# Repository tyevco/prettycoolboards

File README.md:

# prettycoolboards

**Docs site:** <https://tyevco.github.io/prettycoolboards/>

Open hardware boards designed as code. The schematics and PCBs are generated
from Python into KiCad 10, routed with Freerouting plus a grid router, and
gated by ERC, DRC and schematic parity before any fab output is written.
Enclosures and mechanics are in build123d.

## Boards

| Board | Status | |
|---|---|---|
| [PrettyCool Caliper](caliper/README.md) | rev A in design | 150 mm digital caliper: magnetic and capacitive sensing, ESP32-S3 with BLE + Wi-Fi, colour IPS, reading memory, go/no-go, USB-C |
| [PrettyCool Keyboard](keyboard/README.md) | concept: researched, nothing designed | Analog keyboard designed as code: shear keys that point, a haptic thumb wheel, two-host KVM, a generated keywell, and a layout compiler with latency and battery gates. Rev A is a sensing testbed |

## Repository layout

```
tools/        shared Python → KiCad generator toolchain (see tools/README.md)
caliper/      one folder per board: hardware/, firmware/, app/, docs/
keyboard/     concept and research only (docs/), no hardware yet
.vitepress/   docs site (VitePress), published to GitHub Pages by .github/workflows/docs.yml
```

The hardware toolchain runs on Linux: KiCad 10 (`kicad-cli` + `pcbnew`), Java 21 +
Freerouting 2.1, ngspice and build123d. On Windows, run it in WSL.

```sh
npm ci && npm run docs:dev   # preview the docs site locally
```

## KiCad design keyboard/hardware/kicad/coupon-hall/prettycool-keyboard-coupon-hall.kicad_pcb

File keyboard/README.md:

# PrettyCool Keyboard (working name)

A planned analog keyboard designed as code: one layout file in, a gated, JLC-assembled board, case and firmware out.
The plan: keys that also point, and controls that change how they feel to suit what you are doing.

> **Status (2026-11-27): concept and rev A testbed design.** Nothing is built, ordered or measured. This folder holds
> the research, the feature roadmap the owner chose on 2026-11-25, the rev A MCU the owner chose on 2026-11-26
> ([decision record](docs/mcu.md)), three testbed decisions of the same day (no charger on rev A, the slot connector, a
> USB Type-C detect chip), and the owner's seven answers of 2026-11-27 to the [rev A risk register](docs/risks.md)
> (below). The testbed's [SPEC](hardware/design/SPEC.md) is its draft architecture of record. The test coupon and the
> Hall-effect coupon are captured, laid out, routed and gated, and the motherboard schematic is captured (all on
> 2026-11-27); none of them carries the decisions of 2026-11-27 yet, and nothing is built. The firmware (the
> [8 kHz HID proof](firmware/hid8k/README.md) for the Nucleo, the testbed's board support and its bring-up
> application) compiles and has never run on hardware. Every part, figure and claim on these pages is a candidate from
> desk research, to be checked on the rev A testbed.

## Concept renders

Concept sketches from rough build123d models, with illustrative geometry: they show the ideas, not a design, and each
one carries a CONCEPT SKETCH stamp. The [concept renders page](hardware/concept/README.md) has every render and
figure, and the **[3D gallery](https://tyevco.github.io/prettycoolboards/keyboard/gallery/)** has the models to
rotate.

| | |
|---|---|
|  |  |
| *Rev B as sketched: a generated keywell per half (the sketch tents it about 18°, an illustrative constant), a thumb arc, and one haptic thumb wheel (drawn on the left half; which half is not decided). Blue: the shear keys* | *Rev A, the testbed: one motherboard and a plug-in coupon per sensing method, on the owner's 2 × 20, 2.54 mm slot connector. The board sizes are the draft SPEC's "about" figures and the layout is illustrative; the optional KVM coupon is drawn as a ghost* |
|  |  |
| *A shear key, one way it could work: the stem slides inside a carrier hung on flexure posts, so a sideways push moves its magnet over a TMAG5170 3-axis Hall sensor* | *The left half's parts stack. Sizes are placeholders, and the switches are drawn socketless, though hot-swap is still an open question ([concept §9](docs/concept.md#_9-open-questions))* |

## The idea in one table

| | |
|---|---|
| What it is not | Another Hall-effect gaming board. Adjustable actuation, rapid trigger, 8 kHz polling, SOCD and browser configurators are now table stakes ([research](docs/research.md#what-no-longer-differentiates)) |
| What it is | A planned integration that the desk research found in no single product or project (four of the five sceptics could not search the web): keys that point (shear keys), a profile-driven haptic thumb wheel, two wired hosts at once, a firmware that explains and tunes its own tap/hold decisions, and a layout compiler whose releases are gated on wiring, DRC, placement, latency and battery life |
| Priorities | All four, by owner decision: daily driver (programming), gaming / performance, ergonomics, and a showcase for the toolchain |
| Form factor | Open: the features decide. The roadmap points to a split with a generated keywell |
| Ambition | Moonshot: novel sensing and mechanics that may take several revisions, but it must end up a usable daily driver |

## Decisions so far (owner, 2026-11-25 to 2026-11-27)

| Question | Decision |
|---|---|
| Form factor | Open, let the features decide |
| Priorities | Daily driver, gaming, ergonomics, toolchain showcase (all four) |
| Switch technology | Undecided: the rev A testbed compares Hall-effect, TMR, 3-axis Hall and printed inductive coils |
| Ambition | Moonshot |
| Headline hardware | Shear keys, a generated keywell, a haptic thumb wheel, analog sensing from stock switches (all four) |
| Daily-driver features | Two-host KVM, tap/hold flight recorder and tuner, context-aware feel, per-finger analog tuning (all four) |
| Showcase features | Keyboard compiler, latency and battery gates, sensing testbed, fit to your hand (all four) |
| Staging | **Testbed first**: rev A proves the sensing and the compiler on coupons; the keyboard is rev B |
| Firmware | **Custom firmware on Zephyr**, with ZMK-compatible keymap files where possible |
| Platform (MCU) | Rev A: chosen (the next row). Rev B: **the testbed decides.** Rev A measures the sensors' real current; a battery-budget gate picks the rev B chip |
| Rev A MCU: STM32U5A5 (2026-11-26) | **STM32U5A5** (STM32U5A5VJT6, LQFP100, JLC C22455480) on the motherboard, with bring-up on the NUCLEO-U5A5ZJ-Q: of the stocked parts found with a high-speed USB PHY on chip and upstream Zephyr support for it, the one with the strongest analog. Fallback: the NXP i.MX RT1021. The AT32F405, the candidate until then, was dropped for having no upstream Zephyr. Before the schematic: reserve the MCUs, and prove 8 kHz HID on the Nucleo ([decision record](docs/mcu.md)) |
| Rev B side track (2026-11-26) | An nRF54LM20 dev kit (XIAO nRF54LM20A or nRF54LM20 DK) measures 8 kHz HID together with BLE, and the radio current, for the battery gate. The nRF54LM20A is the rev B front-runner; the gate still decides |
| Testbed form | **A motherboard plus plug-in coupons**, each coupon generated by the compiler |
| Rev A power (2026-11-26) | **No battery and no charger on rev A**: the charger is deferred to rev B by the owner's choice. **USB-C input** behind an input breaker of about 3.3 A, with a **USB Type-C detect chip on I2C** that reads the current the source advertises (Default, 1.5 A or 3.0 A), so that the firmware sets the board's power budget itself; it uses no MCU pin. The SPEC's candidate chip is TI's TUSB320LAI ([SPEC §3.8](hardware/design/SPEC.md#_3-8-usb-type-c-detect-u-cc)) |
| Rev A slot connector (2026-11-26) | **2 × 20 at 2.54 mm**: a female through-hole socket on the motherboard, a male header on each coupon. The board sizes follow from it (motherboard about 190 × 150 mm, coupons about 58 × 60 and 80 × 60 mm); layout sets the exact outlines |
| Rev A in two stages (2026-11-27, D1) | **A1** (the motherboard, the test coupon and the Hall coupon) is released, ordered and brought up first; **A2** (the haptics, coil, shear and TMR coupons and the latency rig) is designed after A1 and ordered later, and must not hold A1 back. The optional KVM coupon is out of this release ([SPEC §1](hardware/design/SPEC.md#_1-purpose-and-what-rev-a-must-prove)) |
| The slot key (2026-11-27, D2) | **Keyed at pin 39**: no pin 39 on any coupon, socket hole 39 plugged, unconnected on both sides; never keyed at pin 2 as well |
| The slot guard (2026-11-27, D3) | **100 Ω in series at each socket** on CS0_N, CS1_N, IRQ_N and G0–G3, and on S5's G4/G5: plain resistors, no TVS arrays; the lanes keep their 47 Ω + 1 nF |
| Power fixes (2026-11-27, D4) | The input breaker's power-good divider 100 k / 44.2 k (VSYS_PG falls at 3.51–3.64 V); the USB-C load line written down (4.75 V − 0.25 Ω × I at J1); the DRV8316's supply limits from its datasheet; a **0.47 Ω + 10 µF damping leg on VDDA's supply**, picked with a simulation that includes the regulator; Kelvin sense for every current monitor |
| Layout rules (2026-11-27, D5) | Shrouded box headers for the rig and KVM headers; placement rules for the 2 A path and the analog supply; the PCB stack named (JLC04161H-7628) with the USB pair at 0.25 / 0.15 mm (an estimate until JLC's calculator confirms it); the motherboard single-sided; 0.60 / 0.30 mm vias; a release warning on drills under 0.3 mm |
| MCU supply and SPEC fixes (2026-11-27, D6) | **The MCUs come from ST's store**, bought by the owner; the STM32U599VJT6 and STM32U595VJT6 are pin-compatible alternates (not the -Q parts); five SPEC corrections from the risk register and §8.1's Stop 1 sentence; ST's documents to be read first-hand (st.com still did not answer on 2026-11-27) |
| Coupon fixes (2026-11-27, D7) | The test coupon gets a path from the rig's stimulus into a lane; the haptics coupon one or two Hall sites at rev B distances and a filtered DRV2605L supply; the coil coupon tanks above 1 MHz with two capacitor footprints per coil and its own I2C mux as the documented scheme; the TMR part, its magnet and the shear sensor's variant and spacing are picked before those coupons are captured |
| Left open (2026-11-27) | A coupon BOM without its header (for JLC's Economic assembly), a second source for the bus switch, a rule bounding a lane's voltage, the rules to write before the data (the 1 kHz mode, the rig's VBUS source, the condition-2 decision rule, done cards), and LICENSE files and USB PIDs ([risk register](docs/risks.md#changes-recommended-before-ordering)). These decisions are written into the SPEC; none is captured, built or measured yet |

The twelve chosen features in the three groups above:

```mermaid
---
config:
  # the docs theme sets p { line-height: 28px }, which would clip the labels mermaid measured at 1.5;
  # mermaid only colours the root's and the third branch's HTML labels, so the other branches would take the
  # page's text colour, which is light grey on these pastel fills in dark mode
  themeCSS: "p { line-height: inherit; } .mindmap-node .nodeLabel { color: #1a1a1a; }"
  themeVariables:
    git0: "#c3cbf2"
    gitBranchLabel0: "#1a1a1a"
    cScale1: "#a8dcc8"
    cScaleLabel1: "#1a1a1a"
    cScale2: "#f5c9a0"
    cScaleLabel2: "#1a1a1a"
    cScale3: "#cfc2f2"
    cScaleLabel3: "#1a1a1a"
---
mindmap
  root((The 12 chosen<br/>features))
    Headline hardware
      Shear keys
      Generated keywell
      Haptic thumb wheel
      Analog from stock switches
    Daily driver
      Two-host KVM
      Tap/hold flight recorder
      Context-aware feel
      Per-finger analog tuning
    Showcase
      Keyboard compiler
      Latency and battery gates
      Sensing testbed
      Fit to your hand
```

*The twelve features the owner chose on 2026-11-25: headline hardware, daily driver and showcase. It is a plan; none
of them is built.*

## Roadmap

| Rev | What | Proves |
|---|---|---|
| **A: testbed** | Motherboard (STM32U5A5 with high-speed USB, power, the latency rig's hooks) plus plug-in coupons: Hall-effect, TMR, 3-axis shear sites, printed coils, compliant-stop aftertouch, haptic wheel driver and LRA. A key-injector rig for latency. Compiler v0, which generates the coupons | Which sensing to build on, the sensors' real current, shear signal on a centring stem, whether coils can read a stock MX spring, the wheel's power, and the compiler's first gated boards |
| **B: keyboard** | A compiler-generated split with rigid column boards in a generated keywell case, fitted from S/M/L presets or measurements. The winning sensing, shear on 2–4 keys, the thumb wheel, two-host KVM, and the firmware features | A daily driver |
| **C** | A flex keywell, a phone-photo fit, and analog from stock switches if the rev A coil coupon shows a usable signal | The moonshots that survive rev A |

The same staging with its go/no-go points:

```mermaid
---
config:
  # the docs theme sets p { line-height: 28px }, which would clip the labels mermaid measured at 1.5
  themeCSS: "p { line-height: inherit; }"
  flowchart:
    wrappingWidth: 400
---
flowchart TB
  A["Rev A: testbed<br/>STM32U5A5 motherboard<br/>+ plug-in coupons<br/>latency rig, compiler v0"]
  GA{"Gate A<br/>rev A done?"}
  CK["Rev A is done when:<br/>- each coupon: measured current and noise<br/>- coil coupon: yes or no on stock springs<br/>- shear coupon: can a centring stem point?<br/>- wheel: measured peak and average current<br/>- battery gate picks the rev B chip<br/>- compiler generated and gated every coupon"]:::note
  B["Rev B: keyboard<br/>generated split, rigid column boards<br/>winning sensing, shear on 2–4 keys<br/>thumb wheel, two-host KVM"]
  CX["coils dropped"]
  GB{"Gate B<br/>daily driver?"}
  FLEX["flex only after the<br/>bent-state gate works"]:::note
  C["Rev C: the moonshots that survive<br/>flex keywell, phone-photo fit,<br/>analog from stock switches"]

  A --> GA
  CK -.- GA
  GA -->|"go"| B
  GA -->|"coil coupon: no"| CX
  GA -->|"coil coupon: yes"| C
  B --> GB
  GB -->|"go"| C
  FLEX -.- C

  classDef note text-align:left,stroke-dasharray:4 3
```

*Concept sketch of the staging. Rev A must meet every "done when" item in [concept §7](docs/concept.md#_7-rev-a-testbed)
before rev B starts, and the coil coupon alone decides whether analog from stock switches reaches rev C. Rev B has no
written exit criteria yet, so the B gate only restates the roadmap's "a daily driver" and §8's rule that flex waits
for the bent-state gate.*

And where each chosen feature would land, rev by rev:

```mermaid
---
config:
  # the docs theme sets p { line-height: 28px }, which would clip the labels mermaid measured at 1.5
  themeCSS: "p { line-height: inherit; }"
---
flowchart LR
  subgraph RA["Rev A: testbed"]
    direction TB
    a1["shear coupon"]
    a2["wheel + LRA coupon"]
    a3["coil coupon"]
    a4["KVM coupon, if it fits"]
    a5["compiler v0"]
    a6["latency + battery gates"]
    a7["recorder, tuning data"]
  end
  subgraph RB["Rev B: keyboard"]
    direction TB
    b1["shear on 2–4 keys"]
    b2["thumb wheel, profiles"]
    b3["rigid-column keywell"]
    b4["two-host KVM"]
    b5["full compiler"]
    b6["gates on every release"]
    b7["firmware features"]
    b8["S/M/L fit presets"]
  end
  subgraph RC["Rev C"]
    direction TB
    c1["analog from<br/>stock switches"]
    c2["flex keywell"]
    c3["phone-photo fit"]
  end
  a1 --> b1
  a2 --> b2
  a4 --> b4
  a5 --> b5
  a6 --> b6
  a7 --> b7
  a3 -->|"if usable"| c1
  b3 --> c2
  b8 --> c3
```

*Concept sketch of how each chosen feature moves from a rev A coupon to rev B and rev C, following the Stage lines in
[concept.md](docs/concept.md). Nothing here is built.*

## Documentation

| Document | Contents |
|---|---|
| [docs/concept.md](docs/concept.md) | The chosen features: what each one is, what already exists, the risks, and where it lands in the roadmap. The platform and firmware decisions, the conflicts between features, the rev A testbed |
| [docs/mcu.md](docs/mcu.md) | The rev A MCU decision record (2026-11-26): the requirements, the ranked candidates, why the AT32F405 was dropped, the conditions before the schematic, the bring-up risks, the rev B side track, sources |
| [hardware/design/SPEC.md](hardware/design/SPEC.md) | The rev A testbed's draft architecture of record, with the owner's decisions of 2026-11-26 on the charger, the slot connector and USB-C power, and of 2026-11-27 on the risk register (two stages, the slot key, series resistors, power and layout fixes, MCU alternates, coupon fixes) |
| [docs/risks.md](docs/risks.md) | The rev A risk register (2026-11-27): 55 risks from datasheets, source code and arithmetic, none seen on a bench, with the owner's decision on each recommendation and the ones left open |
| [firmware/README.md](firmware/README.md) | The keyboard's Zephyr firmware, one application per folder, pinned to Zephyr v4.5.0. Today one bring-up application |
| [firmware/hid8k/README.md](firmware/hid8k/README.md) | The 8 kHz HID proof for the NUCLEO-U5A5ZJ-Q (condition 2 before the schematic): the firmware, the host tool that measures report rate and jitter, the test procedure and pass criteria. Written and compiled on 2026-11-27, not run on hardware |
| [docs/research.md](docs/research.md) | The landscape (late 2026), what no longer differentiates, the ideas the owner did not pick, with the sceptic's score and case, the method and its caveats, sources; an addendum on the MCU research of 2026-11-26 |
| [hardware/concept/README.md](hardware/concept/README.md) | Concept renders: every concept sketch, model-estimate plot and research figure in one place, with captions and the commands that regenerate them |

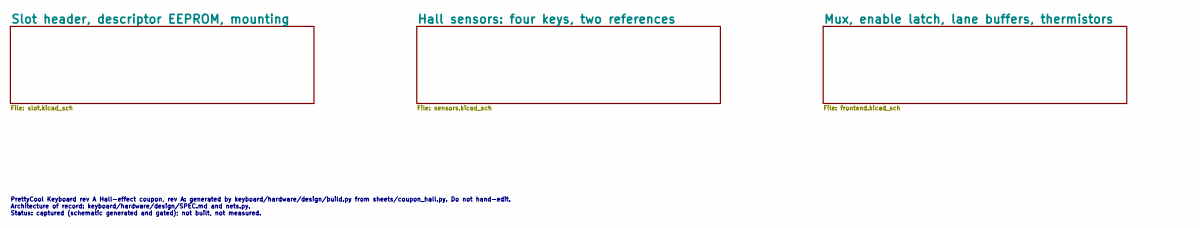
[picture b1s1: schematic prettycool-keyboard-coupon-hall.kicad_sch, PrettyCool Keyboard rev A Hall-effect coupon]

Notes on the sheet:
PrettyCool Keyboard rev A Hall-effect coupon, rev A: generated by keyboard/hardware/design/build.py from sheets/coupon_hall.py. Do not hand-edit. Architecture of record: keyboard/hardware/design/SPEC.md and nets.py. Status: captured (schematic generated and gated); not built, not measured.

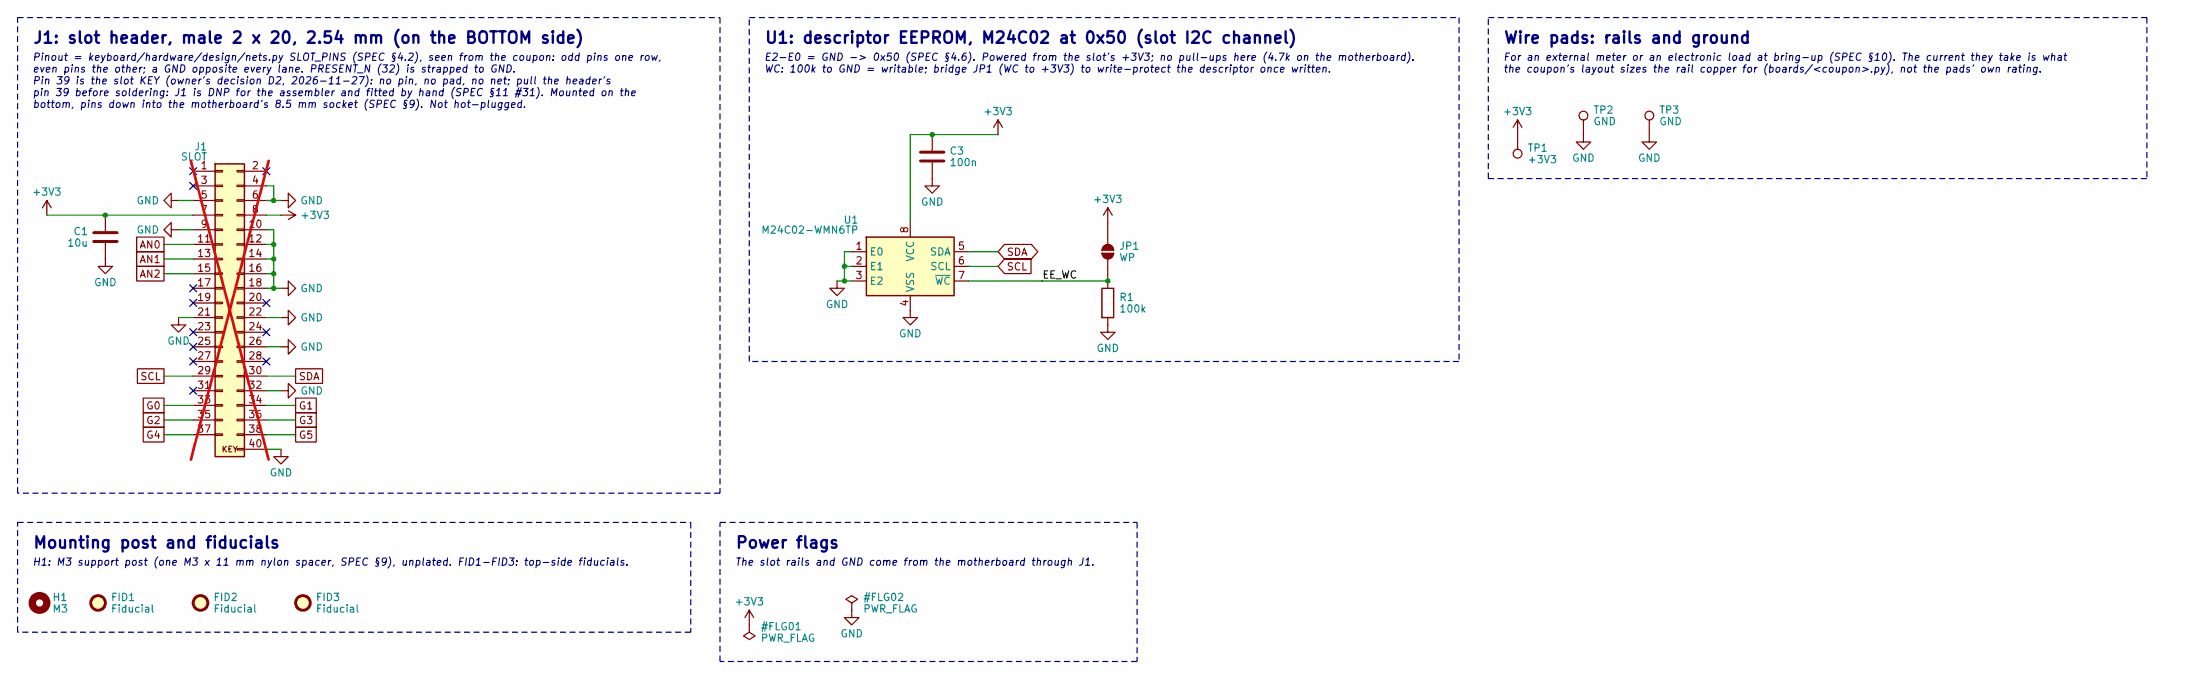
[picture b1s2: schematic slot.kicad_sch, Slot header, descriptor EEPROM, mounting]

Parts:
C1: 10u; C_0603_1608Metric; MPN CL10A106KP8NNNC; LCSC C19702
C3: 100n; C_0402_1005Metric; MPN CL05B104KO5NNNC; LCSC C1525
FID1, FID2, FID3: Fiducial; Fiducial_1mm_Mask2mm
H1: M3; MountingHole_3.2mm_M3
J1: SLOT; PinHeader_2x20_P2.54mm_Vertical; MPN 2541WV-2x20P; LCSC C25503140; not fitted
JP1: WP; SolderJumper-2_P1.3mm_Open_RoundedPad1.0x1.5mm
R1: 100k; R_0402_1005Metric; MPN 0402WGF1003TCE; LCSC C25741
TP1: +3V3; TestPoint_THTPad_D2.0mm_Drill1.0mm
TP2, TP3: GND; TestPoint_THTPad_D2.0mm_Drill1.0mm
U1: M24C02-WMN6TP; SOIC-8_3.9x4.9mm_P1.27mm; MPN M24C02-WMN6TP; LCSC C7562

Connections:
+3V3: C1.1, C3.1, J1.7, J1.8, JP1.2 (B), TP1.1, U1.8 (VCC); also elsewhere on the board
/Slot header, descriptor EEPROM, mounting/EE_WC: JP1.1 (A), R1.1, U1.7 (~WC)
AN0: J1.11; also elsewhere on the board
AN1: J1.13; also elsewhere on the board
AN2: J1.15; also elsewhere on the board
G0: J1.33; also elsewhere on the board
G1: J1.34; also elsewhere on the board
G2: J1.35; also elsewhere on the board
G3: J1.36; also elsewhere on the board
G4: J1.37; also elsewhere on the board
G5: J1.38; also elsewhere on the board
GND: C1.2, C3.2, J1.4, J1.5, J1.6, J1.9, J1.10, J1.12, J1.14, J1.16, J1.18, J1.21, J1.22, J1.26, J1.32, J1.40, R1.2, TP2.1, TP3.1, U1.1 (E0), U1.2 (E1), U1.3 (E2), U1.4 (VSS); also elsewhere on the board
SCL: J1.29, U1.6 (SCL)
SDA: J1.30, U1.5 (SDA)

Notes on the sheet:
J1: slot header, male 2 x 20, 2.54 mm (on the BOTTOM side)
Pinout = keyboard/hardware/design/nets.py SLOT_PINS (SPEC §4.2), seen from the coupon: odd pins one row, even pins the other; a GND opposite every lane. PRESENT_N (32) is strapped to GND. Pin 39 is the slot KEY (owner's decision D2, 2026-11-27): no pin, no pad, no net; pull the header's pin 39 befo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
U1: descriptor EEPROM, M24C02 at 0x50 (slot I2C channel)
E2-E0 = GND -> 0x50 (SPEC §4.6). Powered from the slot's +3V3; no pull-ups here (4.7k on the motherboard). WC: 100k to GND = writable; bridge JP1 (WC to +3V3) to write-protect the descriptor once written.
Wire pads: rails and ground
For an external meter or an electronic load at bring-up (SPEC §10). The current they take is what the coupon's layout sizes the rail copper for (boards/<coupon>.py), not the pads' own rating.
Mounting post and fiducials
H1: M3 support post (one M3 x 11 mm nylon spacer, SPEC §9), unplated. FID1-FID3: top-side fiducials.
Power flags
The slot rails and GND come from the motherboard through J1.

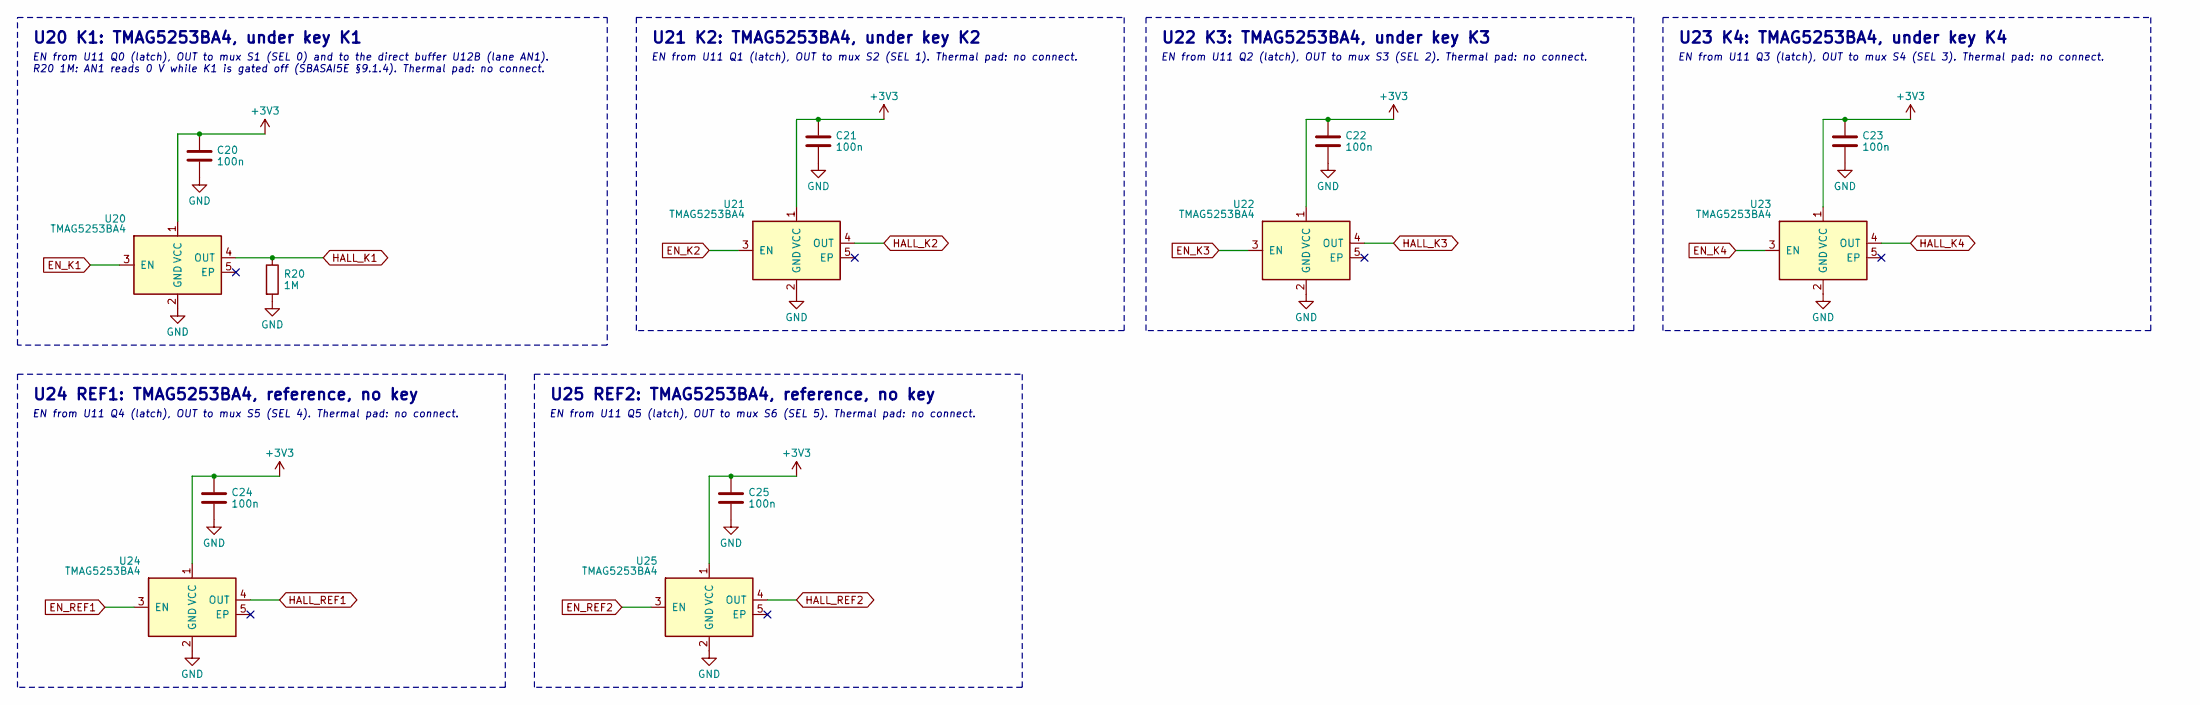
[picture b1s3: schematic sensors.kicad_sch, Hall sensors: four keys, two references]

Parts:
C20, C21, C22, C23, C24, C25: 100n; C_0402_1005Metric; MPN CL05B104KO5NNNC; LCSC C1525
R20: 1M; R_0402_1005Metric; MPN 0402WGF1004TCE; LCSC C26083
U20, U21, U22, U23, U24, U25: TMAG5253BA4; Texas_X2SON-4-1EP_1.1x1.4mm_P0.5mm_EP0.8x0.6mm; MPN TMAG5253BA4IQDMRR; LCSC C22452022

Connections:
+3V3: C20.1, C21.1, C22.1, C23.1, C24.1, C25.1, U20.1 (VCC), U21.1 (VCC), U22.1 (VCC), U23.1 (VCC), U24.1 (VCC), U25.1 (VCC); also elsewhere on the board
EN_K1: U20.3 (EN); also elsewhere on the board
EN_K2: U21.3 (EN); also elsewhere on the board
EN_K3: U22.3 (EN); also elsewhere on the board
EN_K4: U23.3 (EN); also elsewhere on the board
EN_REF1: U24.3 (EN); also elsewhere on the board
EN_REF2: U25.3 (EN); also elsewhere on the board
GND: C20.2, C21.2, C22.2, C23.2, C24.2, C25.2, R20.2, U20.2 (GND), U21.2 (GND), U22.2 (GND), U23.2 (GND), U24.2 (GND), U25.2 (GND); also elsewhere on the board
HALL_K1: R20.1, U20.4 (OUT); also elsewhere on the board
HALL_K2: U21.4 (OUT); also elsewhere on the board
HALL_K3: U22.4 (OUT); also elsewhere on the board
HALL_K4: U23.4 (OUT); also elsewhere on the board
HALL_REF1: U24.4 (OUT); also elsewhere on the board
HALL_REF2: U25.4 (OUT); also elsewhere on the board

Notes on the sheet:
U20 K1: TMAG5253BA4, under key K1
EN from U11 Q0 (latch), OUT to mux S1 (SEL 0) and to the direct buffer U12B (lane AN1). R20 1M: AN1 reads 0 V while K1 is gated off (SBASAI5E §9.1.4). Thermal pad: no connect.
U21 K2: TMAG5253BA4, under key K2
EN from U11 Q1 (latch), OUT to mux S2 (SEL 1). Thermal pad: no connect.
U22 K3: TMAG5253BA4, under key K3
EN from U11 Q2 (latch), OUT to mux S3 (SEL 2). Thermal pad: no connect.
U23 K4: TMAG5253BA4, under key K4
EN from U11 Q3 (latch), OUT to mux S4 (SEL 3). Thermal pad: no connect.
U24 REF1: TMAG5253BA4, reference, no key
EN from U11 Q4 (latch), OUT to mux S5 (SEL 4). Thermal pad: no connect.
U25 REF2: TMAG5253BA4, reference, no key
EN from U11 Q5 (latch), OUT to mux S6 (SEL 5). Thermal pad: no connect.

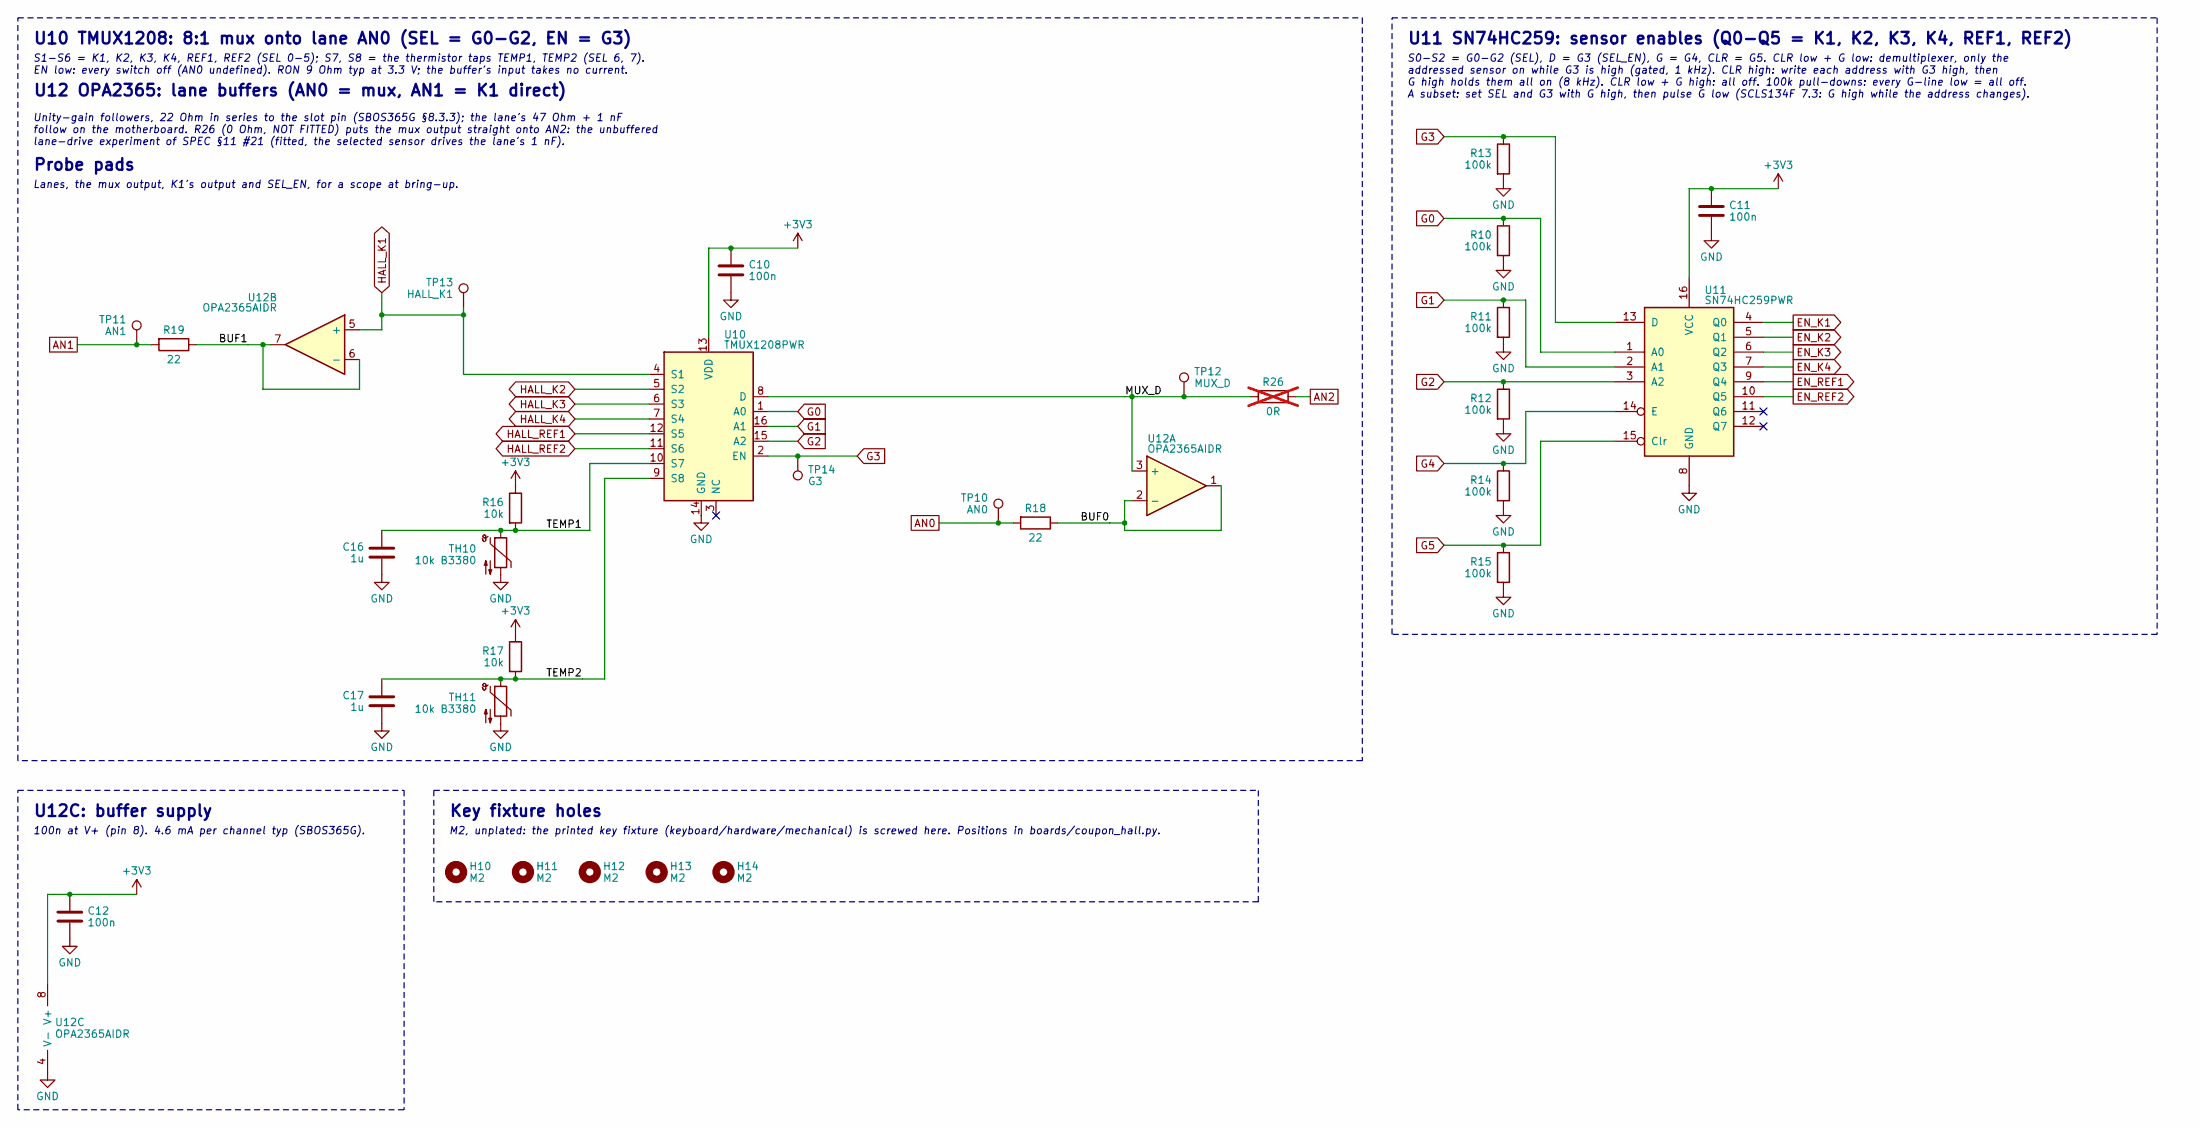
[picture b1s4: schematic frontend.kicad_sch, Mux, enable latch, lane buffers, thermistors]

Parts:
C10, C11, C12: 100n; C_0402_1005Metric; MPN CL05B104KO5NNNC; LCSC C1525
C16, C17: 1u; C_0402_1005Metric; MPN CL05A105KA5NQNC; LCSC C52923
H10, H11, H12, H13, H14: M2; MountingHole_2.2mm_M2
R10, R11, R12, R13, R14, R15: 100k; R_0402_1005Metric; MPN 0402WGF1003TCE; LCSC C25741
R16, R17: 10k; R_0603_1608Metric; MPN RT0603BRD0710KL; LCSC C95204
R18, R19: 22; R_0402_1005Metric; MPN 0402WGF220JTCE; LCSC C25092
R26: 0R; R_0402_1005Metric; MPN 0402WGF0000TCE; LCSC C17168; not fitted
TH10, TH11: 10k B3380; R_0402_1005Metric; MPN NCP15XH103F03RC; LCSC C77131
TP10: AN0; TestPoint_Pad_D1.0mm
TP11: AN1; TestPoint_Pad_D1.0mm
TP12: MUX_D; TestPoint_Pad_D1.0mm
TP13: HALL_K1; TestPoint_Pad_D1.0mm
TP14: G3; TestPoint_Pad_D1.0mm
U10: TMUX1208PWR; TSSOP-16_4.4x5mm_P0.65mm; MPN TMUX1208PWR; LCSC C494728
U11: SN74HC259PWR; TSSOP-16_4.4x5mm_P0.65mm; MPN SN74HC259PWR; LCSC C2652971
U12: OPA2365AIDR; SOIC-8_3.9x4.9mm_P1.27mm; MPN OPA2365AIDR; LCSC C130011

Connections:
+3V3: C10.1, C11.1, C12.1, R16.1, R17.1, U10.13 (VDD), U11.16 (VCC), U12.8 (V+); also elsewhere on the board
/Mux, enable latch, lane buffers, thermistors/BUF0: R18.1, U12.1, U12.2 (-)
/Mux, enable latch, lane buffers, thermistors/BUF1: R19.1, U12.6 (-), U12.7
/Mux, enable latch, lane buffers, thermistors/MUX_D: R26.1, TP12.1, U10.8 (D), U12.3 (+)
/Mux, enable latch, lane buffers, thermistors/TEMP1: C16.1, R16.2, TH10.1, U10.10 (S7)
/Mux, enable latch, lane buffers, thermistors/TEMP2: C17.1, R17.2, TH11.1, U10.9 (S8)
AN0: R18.2, TP10.1; also elsewhere on the board
AN1: R19.2, TP11.1; also elsewhere on the board
AN2: R26.2; also elsewhere on the board
EN_K1: U11.4 (Q0); also elsewhere on the board
EN_K2: U11.5 (Q1); also elsewhere on the board
EN_K3: U11.6 (Q2); also elsewhere on the board
EN_K4: U11.7 (Q3); also elsewhere on the board
EN_REF1: U11.9 (Q4); also elsewhere on the board
EN_REF2: U11.10 (Q5); also elsewhere on the board
G0: R10.1, U10.1 (A0), U11.1 (A0); also elsewhere on the board
G1: R11.1, U10.16 (A1), U11.2 (A1); also elsewhere on the board
G2: R12.1, U10.15 (A2), U11.3 (A2); also elsewhere on the board
G3: R13.1, TP14.1, U10.2 (EN), U11.13 (D); also elsewhere on the board
G4: R14.1, U11.14 (E); also elsewhere on the board
G5: R15.1, U11.15 (Clr); also elsewhere on the board
GND: C10.2, C11.2, C12.2, C16.2, C17.2, R10.2, R11.2, R12.2, R13.2, R14.2, R15.2, TH10.2, TH11.2, U10.14 (GND), U11.8 (GND), U12.4 (V-); also elsewhere on the board
HALL_K1: TP13.1, U10.4 (S1), U12.5 (+); also elsewhere on the board
HALL_K2: U10.5 (S2); also elsewhere on the board
HALL_K3: U10.6 (S3); also elsewhere on the board
HALL_K4: U10.7 (S4); also elsewhere on the board
HALL_REF1: U10.12 (S5); also elsewhere on the board
HALL_REF2: U10.11 (S6); also elsewhere on the board

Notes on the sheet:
U10 TMUX1208: 8:1 mux onto lane AN0 (SEL = G0-G2, EN = G3)
S1-S6 = K1, K2, K3, K4, REF1, REF2 (SEL 0-5); S7, S8 = the thermistor taps TEMP1, TEMP2 (SEL 6, 7). EN low: every switch off (AN0 undefined). RON 9 Ohm typ at 3.3 V; the buffer's input takes no current.
U12 OPA2365: lane buffers (AN0 = mux, AN1 = K1 direct)
Unity-gain followers, 22 Ohm in series to the slot pin (SBOS365G §8.3.3); the lane's 47 Ohm + 1 nF follow on the motherboard. R26 (0 Ohm, NOT FITTED) puts the mux output straight onto AN2: the unbuffered lane-drive experiment of SPEC §11 #21 (fitted, the selected sensor drives the lane's 1 nF).
Probe pads
Lanes, the mux output, K1's output and SEL_EN, for a scope at bring-up.
U12C: buffer supply
100n at V+ (pin 8). 4.6 mA per channel typ (SBOS365G).
U11 SN74HC259: sensor enables (Q0-Q5 = K1, K2, K3, K4, REF1, REF2)
S0-S2 = G0-G2 (SEL), D = G3 (SEL_EN), G = G4, CLR = G5. CLR low + G low: demultiplexer, only the addressed sensor on while G3 is high (gated, 1 kHz). CLR high: write each address with G3 high, then G high holds them all on (8 kHz). CLR low + G high: all off. 100k pull-downs: every G-line low = all 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
Key fixture holes
M2, unplated: the printed key fixture (keyboard/hardware/mechanical) is screwed here. Positions in boards/coupon_hall.py.

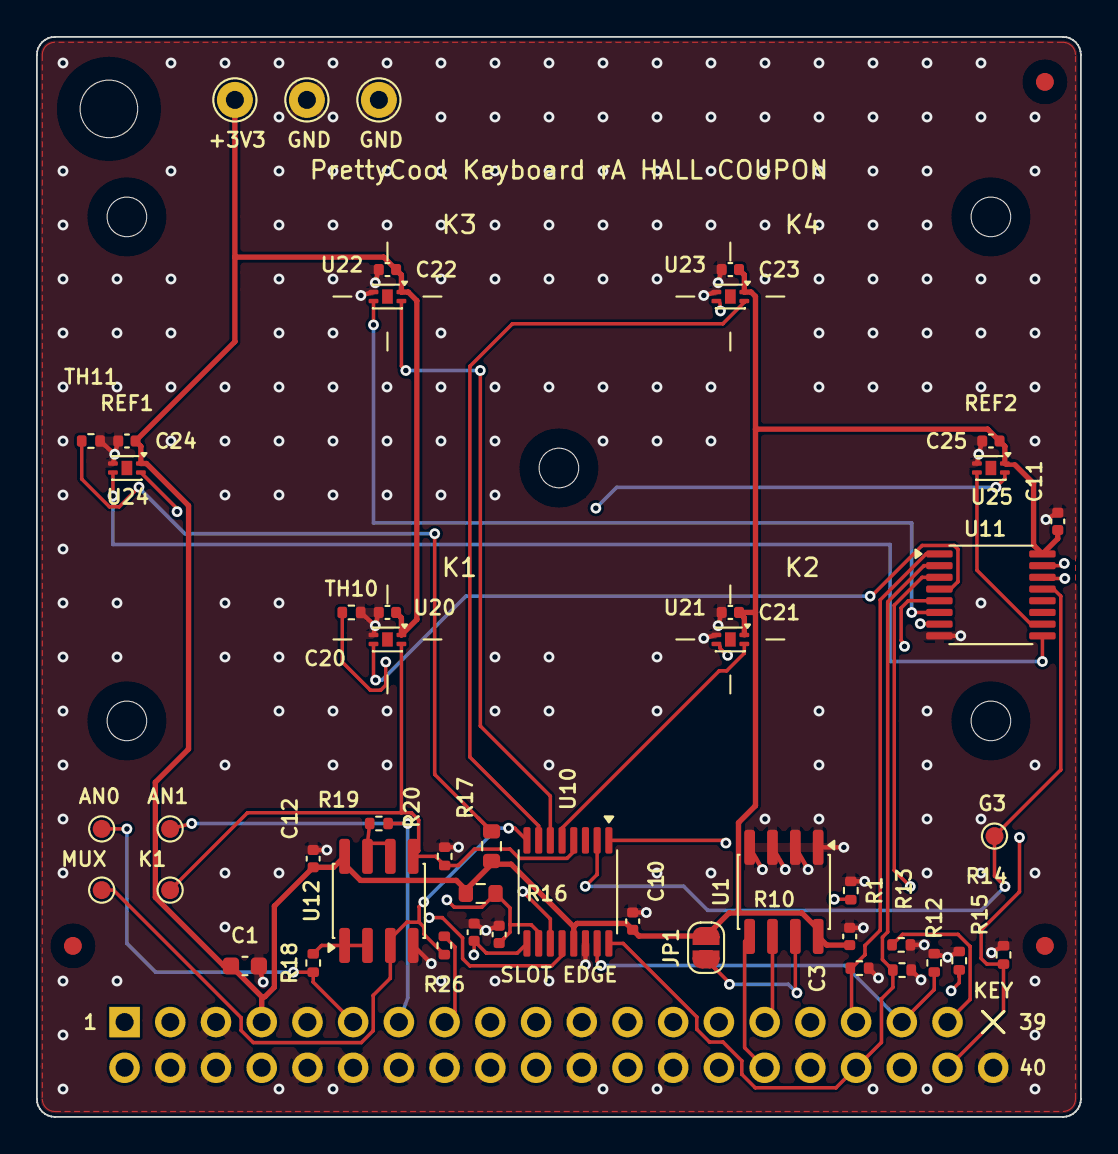
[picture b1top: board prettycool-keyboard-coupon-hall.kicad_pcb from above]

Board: 4 copper layers, 58.0 x 60.0 mm, 57 parts (1 on the bottom side), 31 nets.

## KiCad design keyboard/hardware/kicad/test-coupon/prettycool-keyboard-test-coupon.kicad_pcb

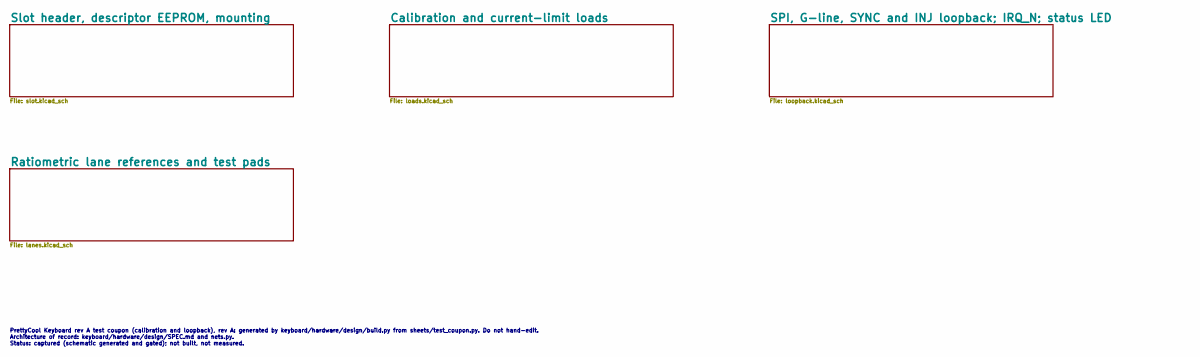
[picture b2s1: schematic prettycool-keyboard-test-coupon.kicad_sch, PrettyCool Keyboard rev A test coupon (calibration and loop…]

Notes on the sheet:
PrettyCool Keyboard rev A test coupon (calibration and loopback), rev A: generated by keyboard/hardware/design/build.py from sheets/test_coupon.py. Do not hand-edit. Architecture of record: keyboard/hardware/design/SPEC.md and nets.py. Status: captured (schematic generated and gated); not built, no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

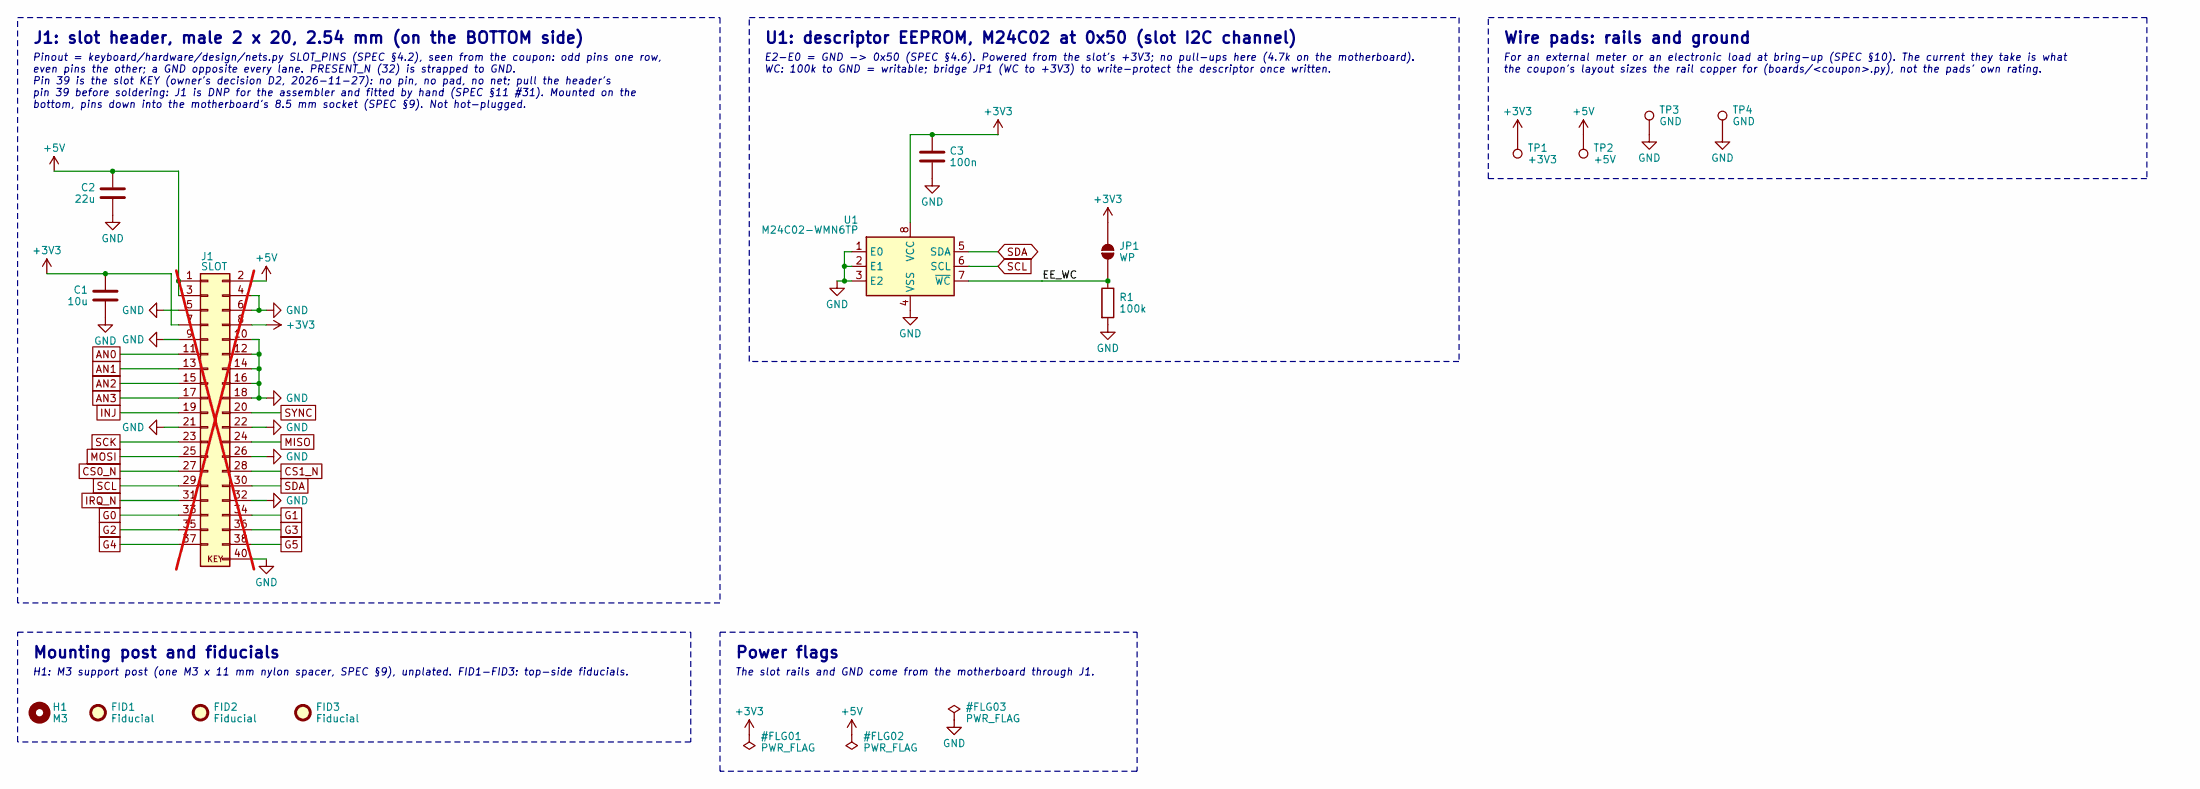
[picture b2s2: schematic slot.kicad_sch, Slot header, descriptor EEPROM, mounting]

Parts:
C1: 10u; C_0603_1608Metric; MPN CL10A106KP8NNNC; LCSC C19702
C2: 22u; C_0805_2012Metric; MPN CL21A226MAQNNNE; LCSC C45783
C3: 100n; C_0402_1005Metric; MPN CL05B104KO5NNNC; LCSC C1525
FID1, FID2, FID3: Fiducial; Fiducial_1mm_Mask2mm
H1: M3; MountingHole_3.2mm_M3
J1: SLOT; PinHeader_2x20_P2.54mm_Vertical; MPN 2541WV-2x20P; LCSC C25503140; not fitted
JP1: WP; SolderJumper-2_P1.3mm_Open_RoundedPad1.0x1.5mm
R1: 100k; R_0402_1005Metric; MPN 0402WGF1003TCE; LCSC C25741
TP1: +3V3; TestPoint_THTPad_D2.0mm_Drill1.0mm
TP2: +5V; TestPoint_THTPad_D2.0mm_Drill1.0mm
TP3, TP4: GND; TestPoint_THTPad_D2.0mm_Drill1.0mm
U1: M24C02-WMN6TP; SOIC-8_3.9x4.9mm_P1.27mm; MPN M24C02-WMN6TP; LCSC C7562

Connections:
+3V3: C1.1, C3.1, J1.7, J1.8, JP1.2 (B), TP1.1, U1.8 (VCC); also elsewhere on the board
+5V: C2.1, J1.1, J1.2, J1.3, TP2.1; also elsewhere on the board
/Slot header, descriptor EEPROM, mounting/EE_WC: JP1.1 (A), R1.1, U1.7 (~WC)
AN0: J1.11; also elsewhere on the board
AN1: J1.13; also elsewhere on the board
AN2: J1.15; also elsewhere on the board
AN3: J1.17; also elsewhere on the board
CS0_N: J1.27; also elsewhere on the board
CS1_N: J1.28; also elsewhere on the board
G0: J1.33; also elsewhere on the board
G1: J1.34; also elsewhere on the board
G2: J1.35; also elsewhere on the board
G3: J1.36; also elsewhere on the board
G4: J1.37; also elsewhere on the board
G5: J1.38; also elsewhere on the board
GND: C1.2, C2.2, C3.2, J1.4, J1.5, J1.6, J1.9, J1.10, J1.12, J1.14, J1.16, J1.18, J1.21, J1.22, J1.26, J1.32, J1.40, R1.2, TP3.1, TP4.1, U1.1 (E0), U1.2 (E1), U1.3 (E2), U1.4 (VSS); also elsewhere on the board
INJ: J1.19; also elsewhere on the board
IRQ_N: J1.31; also elsewhere on the board
MISO: J1.24; also elsewhere on the board
MOSI: J1.25; also elsewhere on the board
SCK: J1.23; also elsewhere on the board
SCL: J1.29, U1.6 (SCL)
SDA: J1.30, U1.5 (SDA)
SYNC: J1.20; also elsewhere on the board

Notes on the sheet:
J1: slot header, male 2 x 20, 2.54 mm (on the BOTTOM side)
Pinout = keyboard/hardware/design/nets.py SLOT_PINS (SPEC §4.2), seen from the coupon: odd pins one row, even pins the other; a GND opposite every lane. PRESENT_N (32) is strapped to GND. Pin 39 is the slot KEY (owner's decision D2, 2026-11-27): no pin, no pad, no net; pull the header's pin 39 befo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
U1: descriptor EEPROM, M24C02 at 0x50 (slot I2C channel)
E2-E0 = GND -> 0x50 (SPEC §4.6). Powered from the slot's +3V3; no pull-ups here (4.7k on the motherboard). WC: 100k to GND = writable; bridge JP1 (WC to +3V3) to write-protect the descriptor once written.
Wire pads: rails and ground
For an external meter or an electronic load at bring-up (SPEC §10). The current they take is what the coupon's layout sizes the rail copper for (boards/<coupon>.py), not the pads' own rating.
Mounting post and fiducials
H1: M3 support post (one M3 x 11 mm nylon spacer, SPEC §9), unplated. FID1-FID3: top-side fiducials.
Power flags
The slot rails and GND come from the motherboard through J1.

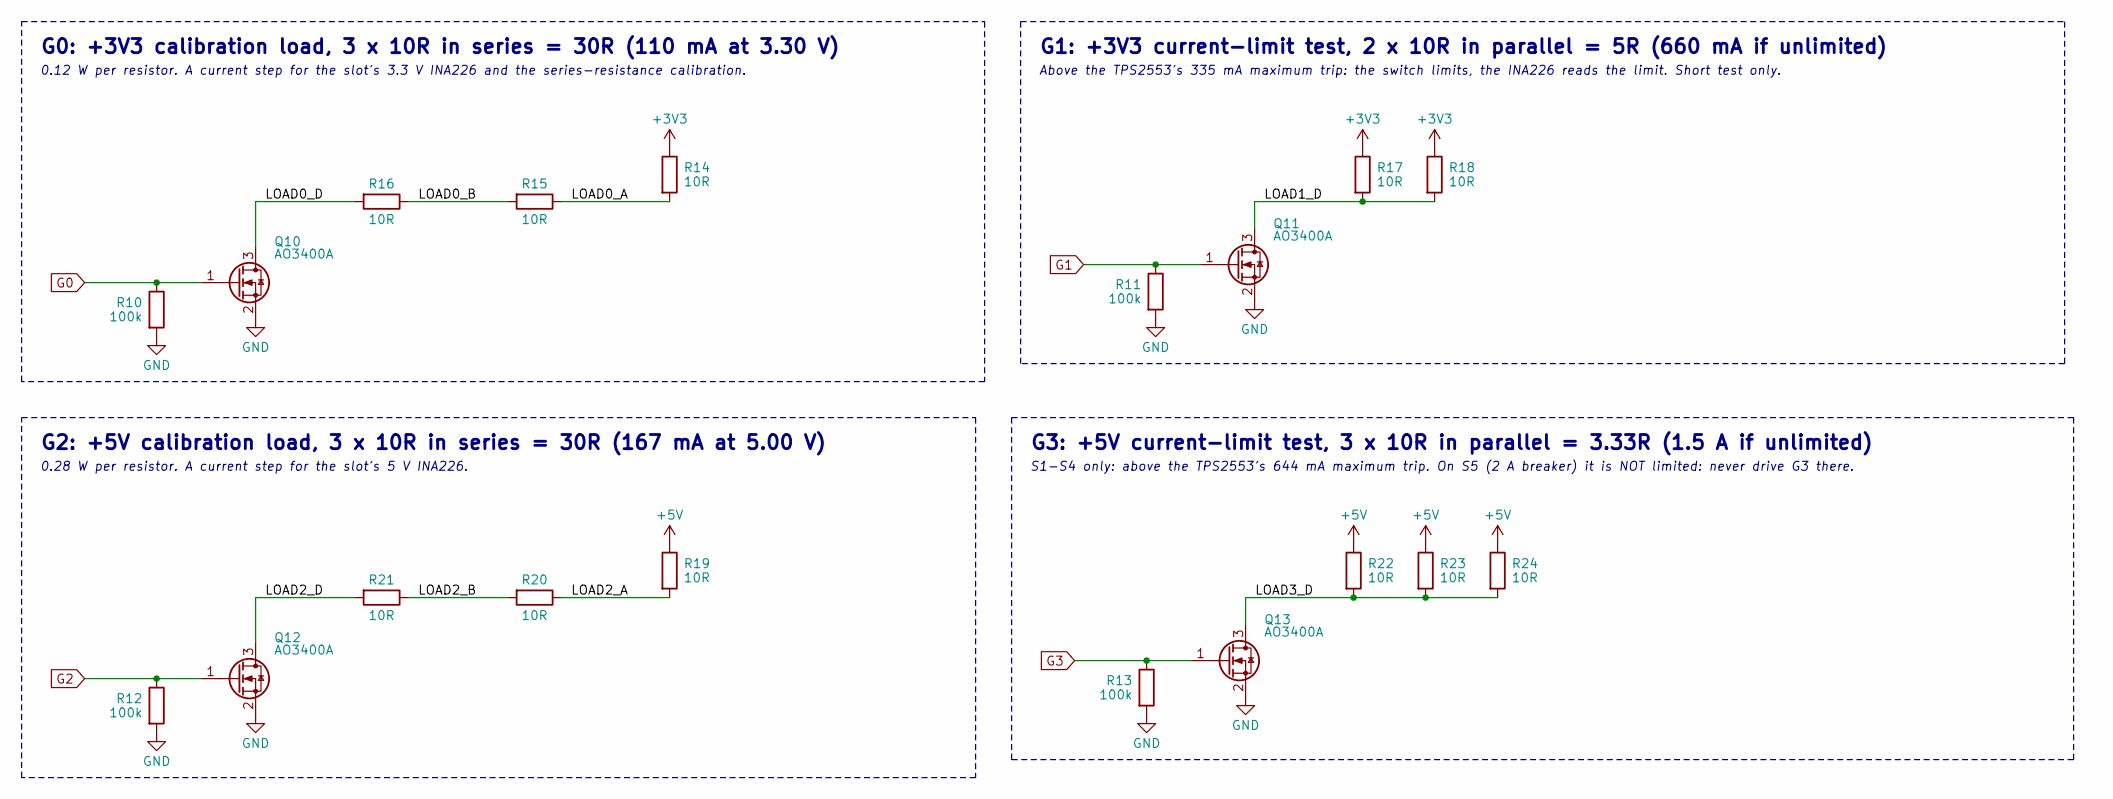
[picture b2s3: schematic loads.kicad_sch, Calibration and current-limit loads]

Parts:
Q10, Q11, Q12, Q13: AO3400A; SOT-23; MPN AO3400A; LCSC C20917
R10, R11, R12, R13: 100k; R_0402_1005Metric; MPN 0402WGF1003TCE; LCSC C25741
R14, R15, R16, R17, R18, R19, R20, R21, R22, R23, R24: 10R; R_2512_6332Metric; MPN 25121WF100JT4E; LCSC C47019

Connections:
+3V3: R14.1, R17.1, R18.1; also elsewhere on the board
+5V: R19.1, R22.1, R23.1, R24.1; also elsewhere on the board
/Calibration and current-limit loads/LOAD0_A: R14.2, R15.1
/Calibration and current-limit loads/LOAD0_B: R15.2, R16.1
/Calibration and current-limit loads/LOAD0_D: Q10.3 (D), R16.2
/Calibration and current-limit loads/LOAD1_D: Q11.3 (D), R17.2, R18.2
/Calibration and current-limit loads/LOAD2_A: R19.2, R20.1
/Calibration and current-limit loads/LOAD2_B: R20.2, R21.1
/Calibration and current-limit loads/LOAD2_D: Q12.3 (D), R21.2
/Calibration and current-limit loads/LOAD3_D: Q13.3 (D), R22.2, R23.2, R24.2
G0: Q10.1 (G), R10.1; also elsewhere on the board
G1: Q11.1 (G), R11.1; also elsewhere on the board
G2: Q12.1 (G), R12.1; also elsewhere on the board
G3: Q13.1 (G), R13.1; also elsewhere on the board
GND: Q10.2 (S), Q11.2 (S), Q12.2 (S), Q13.2 (S), R10.2, R11.2, R12.2, R13.2; also elsewhere on the board

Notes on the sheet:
G0: +3V3 calibration load, 3 x 10R in series = 30R (110 mA at 3.30 V)
0.12 W per resistor. A current step for the slot's 3.3 V INA226 and the series-resistance calibration.
G1: +3V3 current-limit test, 2 x 10R in parallel = 5R (660 mA if unlimited)
Above the TPS2553's 335 mA maximum trip: the switch limits, the INA226 reads the limit. Short test only.
G2: +5V calibration load, 3 x 10R in series = 30R (167 mA at 5.00 V)
0.28 W per resistor. A current step for the slot's 5 V INA226.
G3: +5V current-limit test, 3 x 10R in parallel = 3.33R (1.5 A if unlimited)
S1-S4 only: above the TPS2553's 644 mA maximum trip. On S5 (2 A breaker) it is NOT limited: never drive G3 there.

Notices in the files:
keyboard/firmware/boards/gen_board.py:
w(" * SPDX-License-Identifier: Apache-2.0")
w(" * hardware. SPDX-License-Identifier: Apache-2.0")
hash_comment(m), "# SPDX-License-Identifier: Apache-2.0", "",
